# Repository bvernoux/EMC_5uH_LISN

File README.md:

# 5µH LISN(Line Impedance Stabilization Network)
Open Source Hardware Dual 5µH DC LISN with 10dB Attenuator and Transient Limiter for Spectrum Analyzer EMC work.

A LISN is a [Line Impedance Stabilization Network](https://en.wikipedia.org/wiki/Line_Impedance_Stabilization_Network) used in conducted emissions testing.

The AIM of this Dual LISN is to be used for EMC pre-testing with frequency range 30kHz(or lower) to 110MHz(or up to 150MHz or more).

This open source hardware LISN V1 R0 include following features:
* Designed with fully open source tools like [KiCad 5.99 Nightly](https://www.kicad.org)
* Improvement in this design: 
  * Added simulation with LTSpice of the 10dB Attenuator / Transient Filter (with default 1N4148 and BAV99 see Simu dir)
  * Modified Supply & DUT "+ GND -" to be separated by 19.06mm for 4mm BANANA JACK for BNC adapter
  * Use BAV99 instead of 1N4148W Diodes (improve 10dB Attenuator and Transient Limiter to be flat up to >200MHz)
  * Replace Keystone 575-4 by Keystone 575-8 (as the 575-4 was too short)
  * Added more via for better thermal transfer/decoupling around capacitors ...

* Dual LISN in one aluminum box(Hammond 1590B)
  * Maximum current: 5A
  * Nominal operating voltage range: 0V to 60V DC
  * Include 10dB Attenuator and Transient Limiter for each SMA connector to be connected to a Spectrum Analyzer
    * Max. 1W / 30dBm if 50°C Temperature raise is allowed
    * The Transient limiter is a 9kHz HP filter, which is also a dc block.

This work is heavily based on work from others mainly **Jay_Diddy_B** & **Noy** from EEVBLOG forum.

See all links related to the original Dual 5µH LISN:
* https://www.eevblog.com/forum/projects/5uh-lisn-for-spectrum-analyzer-emcemi-work/75/
* https://www.eevblog.com/forum/projects/5uh-lisn-for-spectrum-analyzer-emcemi-work/msg3420102/#msg3420102

Video related to EMC Conducted Emissions / LISN:
* Rohde Schwarz video Understanding LISNs: 
  * This video explains the design and function of a LISN (line impedance stabilization network) and how LISNs are used in conducted EMC testing.
  * https://www.youtube.com/watch?v=QPJzp66Yvzs
* EMC Conducted Emissions: How to connect and set up a LISN:
  * In this video Dr. Ali Shirsavar shows how you can connect and set up a LISN ready for pre-compliance testing of EMC conducted emissions.
  * https://www.youtube.com/watch?v=28oDdL9RnWM

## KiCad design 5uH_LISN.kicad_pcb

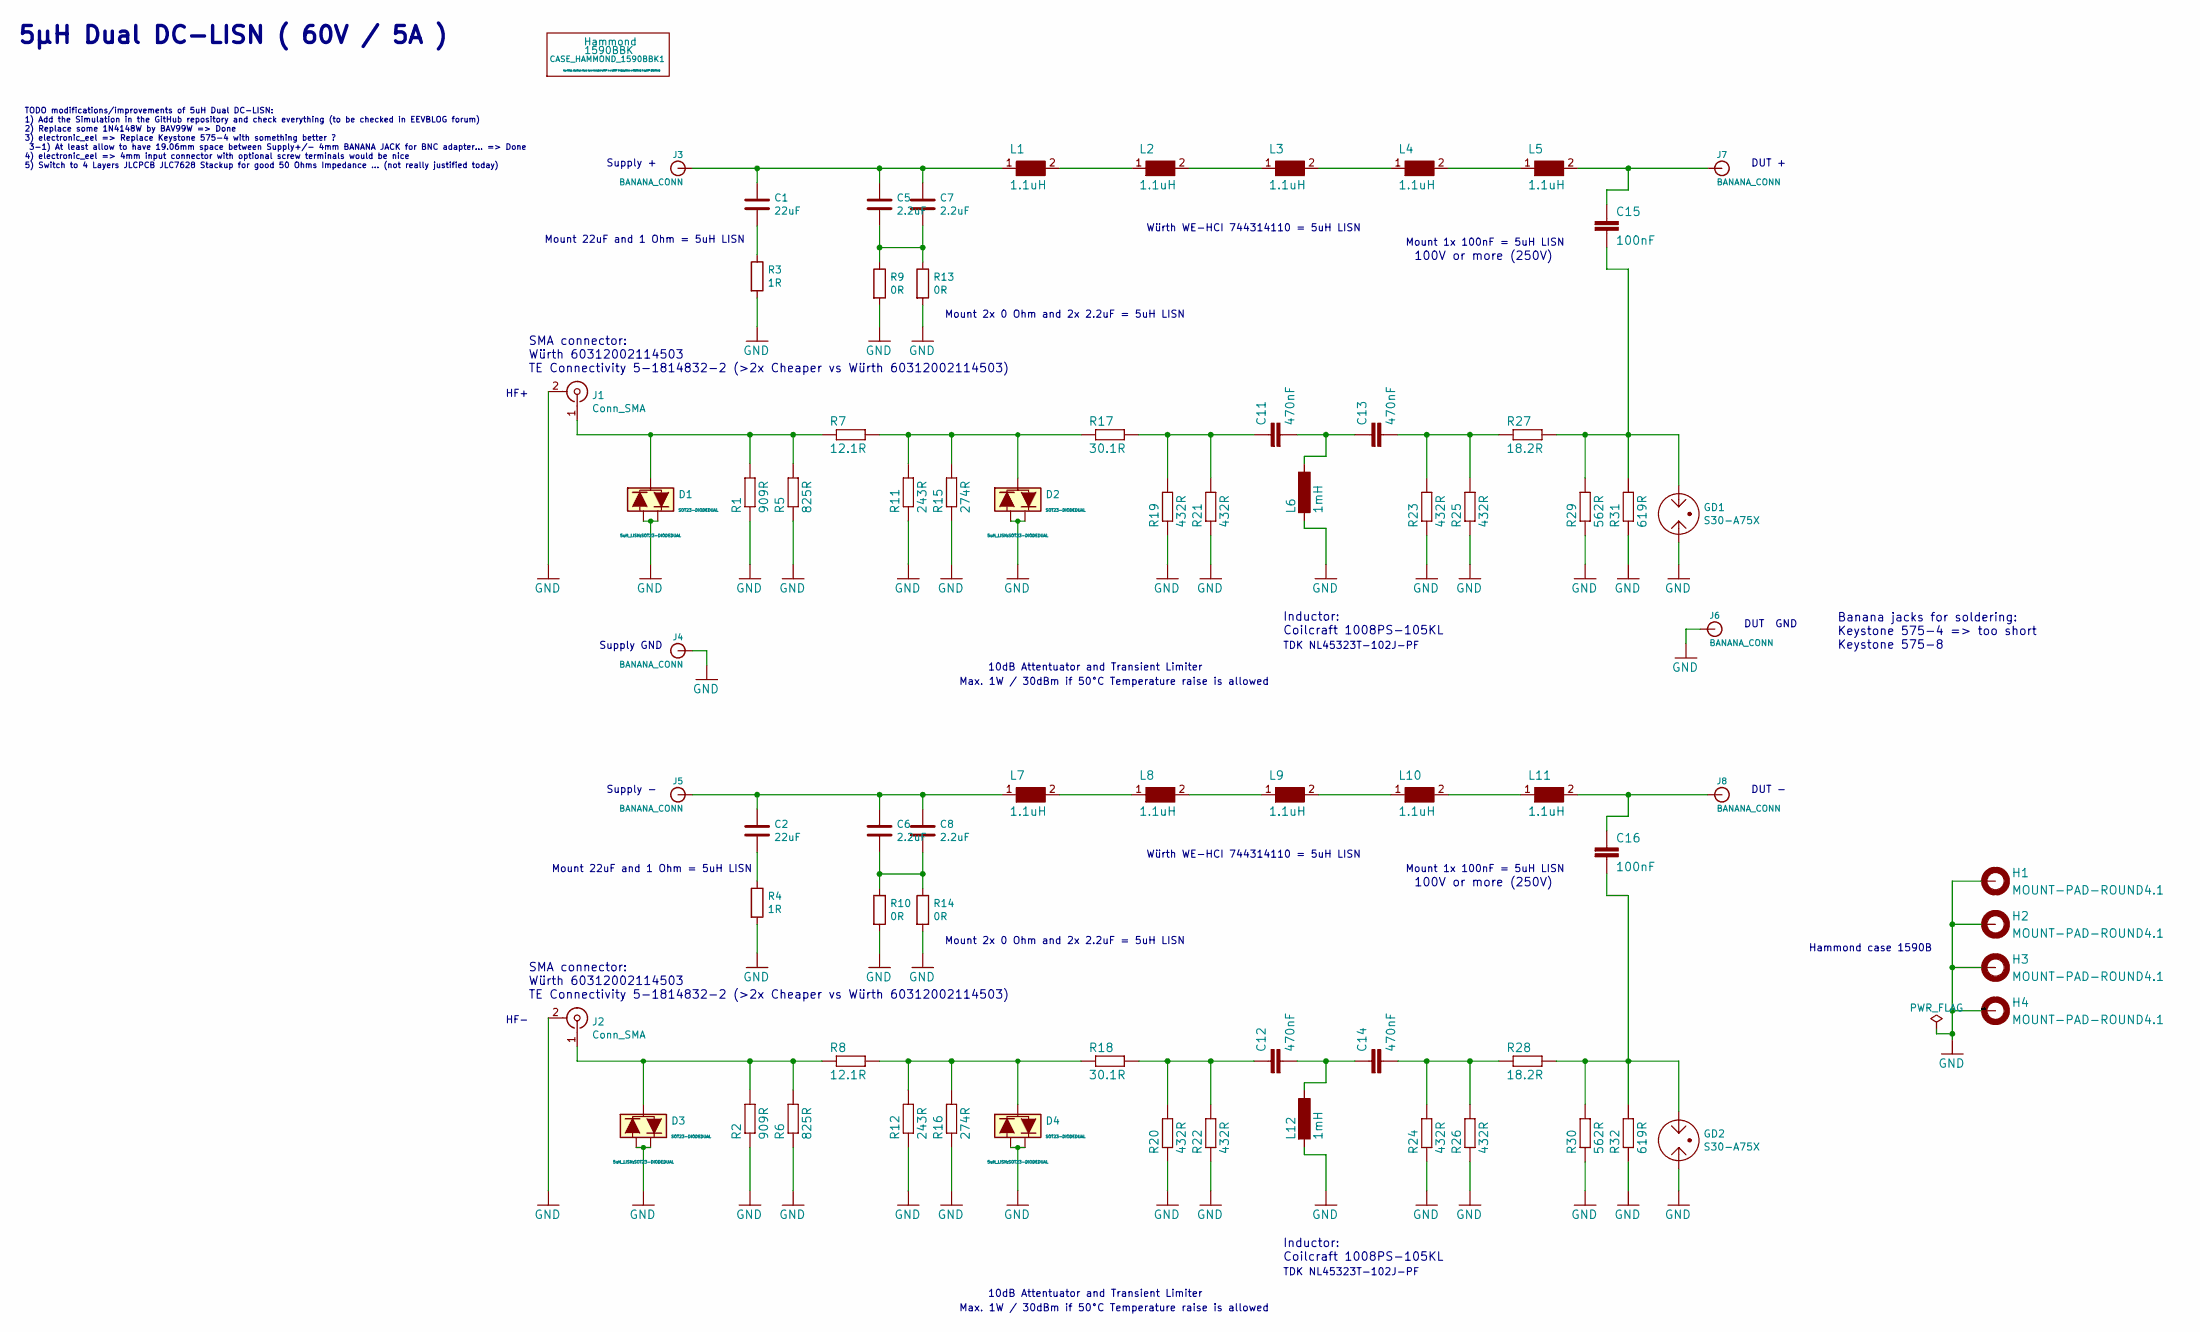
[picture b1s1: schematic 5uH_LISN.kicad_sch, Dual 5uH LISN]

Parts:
C1, C2: 22uF; C_2220_5650Metric
C5, C6, C7, C8: 2.2uF; C_1210_3225Metric
C11, C12, C13, C14: 470nF; C_0805_2012Metric
C15, C16: 100nF; C_1206_3216Metric
CASE_HAMMOND_1590BBK1: (no value)
D1, D2, D3, D4: SOT23-DIODEDUAL; LCSC C2500
GD1, GD2: S30-A75X; S30-A400X
H1, H2, H3, H4: MOUNT-PAD-ROUND4.1; 4,1-PAD
J1, J2: Conn_SMA; SMA_Wurth_60312002114503_Vertical
J3, J4, J5, J6, J7, J8: BANANA_CONN
L1, L2, L3, L4, L5, L7, L8, L9, L10, L11: 1.1uH; WE-HCI_7030_7040_7050
L6, L12: 1mH; COILCRAFT_1008PS
R1, R2: 909R; R_0805_2012Metric
R3, R4: 1R; R_1218_3246Metric
R5, R6: 825R; R_0805_2012Metric
R7, R8: 12.1R; R_1206_3216Metric
R9, R10, R13, R14: 0R; R_1206_3216Metric
R11, R12: 243R; R_0805_2012Metric
R15, R16: 274R; R_0805_2012Metric
R17, R18: 30.1R; R_1206_3216Metric
R19, R20, R21, R22, R23, R24, R25, R26: 432R; R_0805_2012Metric
R27, R28: 18.2R; R_1206_3216Metric
R29, R30: 562R; R_0805_2012Metric
R31, R32: 619R; R_0805_2012Metric

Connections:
GND: D1.1, D1.2, D2.1, D2.2, D3.1, D3.2, D4.1, D4.2, GD1.1, GD2.1, H1.B4,1 (MOUNT), H2.B4,1 (MOUNT), H3.B4,1 (MOUNT), H4.B4,1 (MOUNT), J1.2 (Ext), J2.2 (Ext), J4.P$1 (1), J6.P$1 (1), L6.P$2 (2), L12.P$2 (2), R1.1, R2.1, R3.2, R4.2, R5.1, R6.1, R9.2, R10.2, R11.1, R12.1, R13.2, R14.2, R15.1, R16.1, R19.1, R20.1, R21.1, R22.1, R23.1, R24.1, R25.1, R26.1, R29.1, R30.1, R31.1, R32.1
unnamed: C1.1, C5.1, C7.1, J3.P$1 (1), L1.1
unnamed: C1.2, R3.1
unnamed: C2.1, C6.1, C8.1, J5.P$1 (1), L7.1
unnamed: C2.2, R4.1
unnamed: C5.2, C7.2, R9.1, R13.1
unnamed: C6.2, C8.2, R10.1, R14.1
unnamed: C11.1, R17.2, R19.2, R21.2
unnamed: C11.2, C13.1, L6.P$1 (1)
unnamed: C12.1, R18.2, R20.2, R22.2
unnamed: C12.2, C14.1, L12.P$1 (1)
unnamed: C13.2, R23.2, R25.2, R27.1
unnamed: C14.2, R24.2, R26.2, R28.1
unnamed: C15.1, J7.P$1 (1), L5.2
unnamed: C15.2, GD1.2, R27.2, R29.2, R31.2
unnamed: C16.1, J8.P$1 (1), L11.2
unnamed: C16.2, GD2.2, R28.2, R30.2, R32.2
unnamed: D1.3, J1.1 (In), R1.2, R5.2, R7.1
unnamed: D2.3, R7.2, R11.2, R15.2, R17.1
unnamed: D3.3, J2.1 (In), R2.2, R6.2, R8.1
unnamed: D4.3, R8.2, R12.2, R16.2, R18.1
unnamed: L1.2, L2.1
unnamed: L2.2, L3.1
unnamed: L3.2, L4.1
unnamed: L4.2, L5.1
unnamed: L7.2, L8.1
unnamed: L8.2, L9.1
unnamed: L9.2, L10.1
unnamed: L10.2, L11.1

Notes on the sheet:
10dB Attentuator and Transient Limiter
Inductor: Coilcraft 1008PS-105KL
Supply -
100V or more (250V)
SMA connector: Würth 60312002114503 TE Connectivity 5-1814832-2 (>2x Cheaper vs Würth 60312002114503)
Max. 1W / 30dBm if 50°C Temperature raise is allowed
Würth WE-HCI 744314110 = 5uH LISN
Mount 1x 100nF = 5uH LISN
5µH Dual DC-LISN ( 60V / 5A )
Mount 22uF and 1 Ohm = 5uH LISN
TDK NL45323T-102J-PF
DUT +
Supply +
DUT GND
Mount 2x 0 Ohm and 2x 2.2uF = 5uH LISN
Hammond case 1590B
TODO modifications/improvements of 5uH Dual DC-LISN: 1) Add the Simulation in the GitHub repository and check everything (to be checked in EEVBLOG forum) 2) Replace some 1N4148W by BAV99W => Done 3) electronic_eel => Replace Keystone 575-4 with something better ? 3-1) At least allow to have 19.06mm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
Banana jacks for soldering: Keystone 575-4 => too short Keystone 575-8
Supply GND
HF-
HF+
DUT -

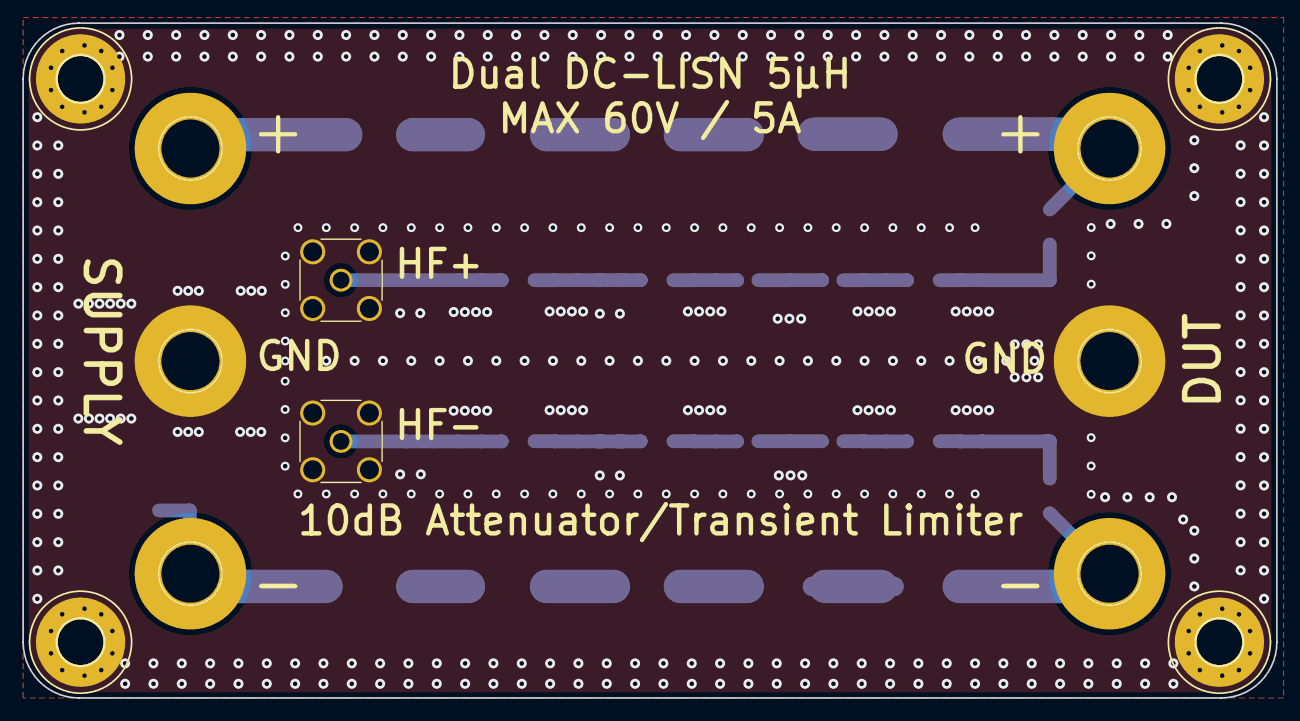
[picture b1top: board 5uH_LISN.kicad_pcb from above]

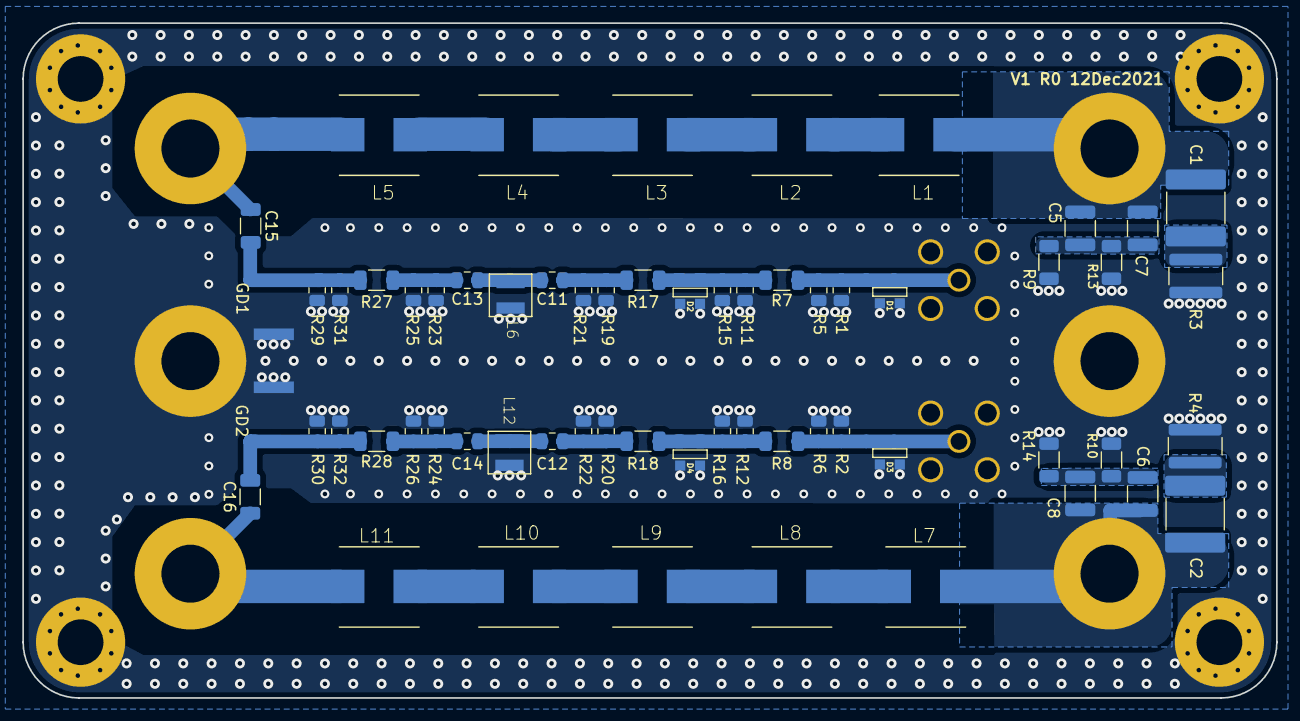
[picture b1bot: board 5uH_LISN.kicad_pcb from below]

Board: 2 copper layers, 112.4 x 60.5 mm, 74 parts (62 on the bottom side), 29 nets.

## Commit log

2021-09-01 First Import KiCad 6 open source hardware 5uH Dual LISN based on work from Jay_Diddy_B & Noy from EEVBLOG forum.
2021-09-01 Create LICENSE
2021-12-10 LISN V1 R0 * Added simulation with LTSpice of the 10dB Attenuator / Transient Filter (with default 1N4148 and BAV99) * Replaced some 1N4148W by BAV99 from Nexperia (to reach up to 400MHz flat 10dB At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
2021-12-10 LISN V1 R0 (pre-release additions) * Add Picture of the PCB Top/Bottom * Add Schematic (5uH_LISN_V1_R0_schematic.pdf)
2021-12-12 Fixed issue https://github.com/bvernoux/EMC_5uH_LISN/issues/4 Remove bottom layer soldermask on PCB edge for proper grounding to case
2023-09-14 Add directory with Gerber files, IPC356, BOM(csv) and ZofzPCB portable v2.0.1.0 ".camset"
